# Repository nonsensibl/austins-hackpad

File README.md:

I just created a small macro pad with 8 switches and 8 rgb LEDs! I am a beginner and this is my first project.

I built this project because I have been very interested in the custom keyboard community for a while now and want to try my hands at it. I found this opportunity off of Instagram and I though it was a very cool thing I could do!

To use this, flash the firmware onto the macro pad and assemble with the sandwich mount design. The switches and LEDs need to be soldered onto the PCB and the keycaps go on at the end.

Challenges:

First: PCB design: KiCad

I had never touched a CAD software let alone designed a PCB. It started off generally easy with the PCB schematic which was self explanatory. However, next was the PCB editor. I spent almost 6 hours on this step. At first my switches and LEDs were in the wrong order, you couldn’t zigzag the LEDs or switches or else you would have a very hard time routing the PCB. Through trial and error, I learned how to route the PCB. 

Although it didn’t look the prettiest, I was proud of what I’d done. I learned some valuable problem solving skills and some very useful things from this. It took a lot of logic to figure out the routing. I also learned that the voltage and ground lines could be linked up line to line.

Second: Case Design

This was my first time doing any sort of 3D design. I first used Fusion360 but due to its limited capabilities, I decided to switch to Onshape. The design was actually fairly difficult and time consuming. This was also where the most math was used to center all the cutouts and make sure the clearances were correct. Compared to the PCB, it was less difficult but more time consuming.

https://cad.onshape.com/documents/ae2a962784265a0a15a314a3/w/fd7747368c903f62fc80b54c/e/c2a1514edb9aca260c24a683?renderMode=0&uiState=69d857150cda52f2ac39aa26 

Third: Firmware

This was actually the easiest part of the project. I just mapped each key to be an arbitrary macro key so the coding was very straight forward.

Summary:

I enjoyed this project a lot and learned a lot about 3D design, PCB design, and coding which I hope to use in other projects!

Materials: 
BOM:
8x Cherry MX Switches
8x SK6812 MINI-E LEDs
1x Seeeduino XIAO RP2040
8x Blank DCA Keycaps
4x M3 Screws
(Included in the kit)

Custom PCB
($5.12 from the HCB grant will be used)

Top Plate.step 
Bottom Plate.step
(Will be printed through printing legion) 

Others:
KMK Firmware

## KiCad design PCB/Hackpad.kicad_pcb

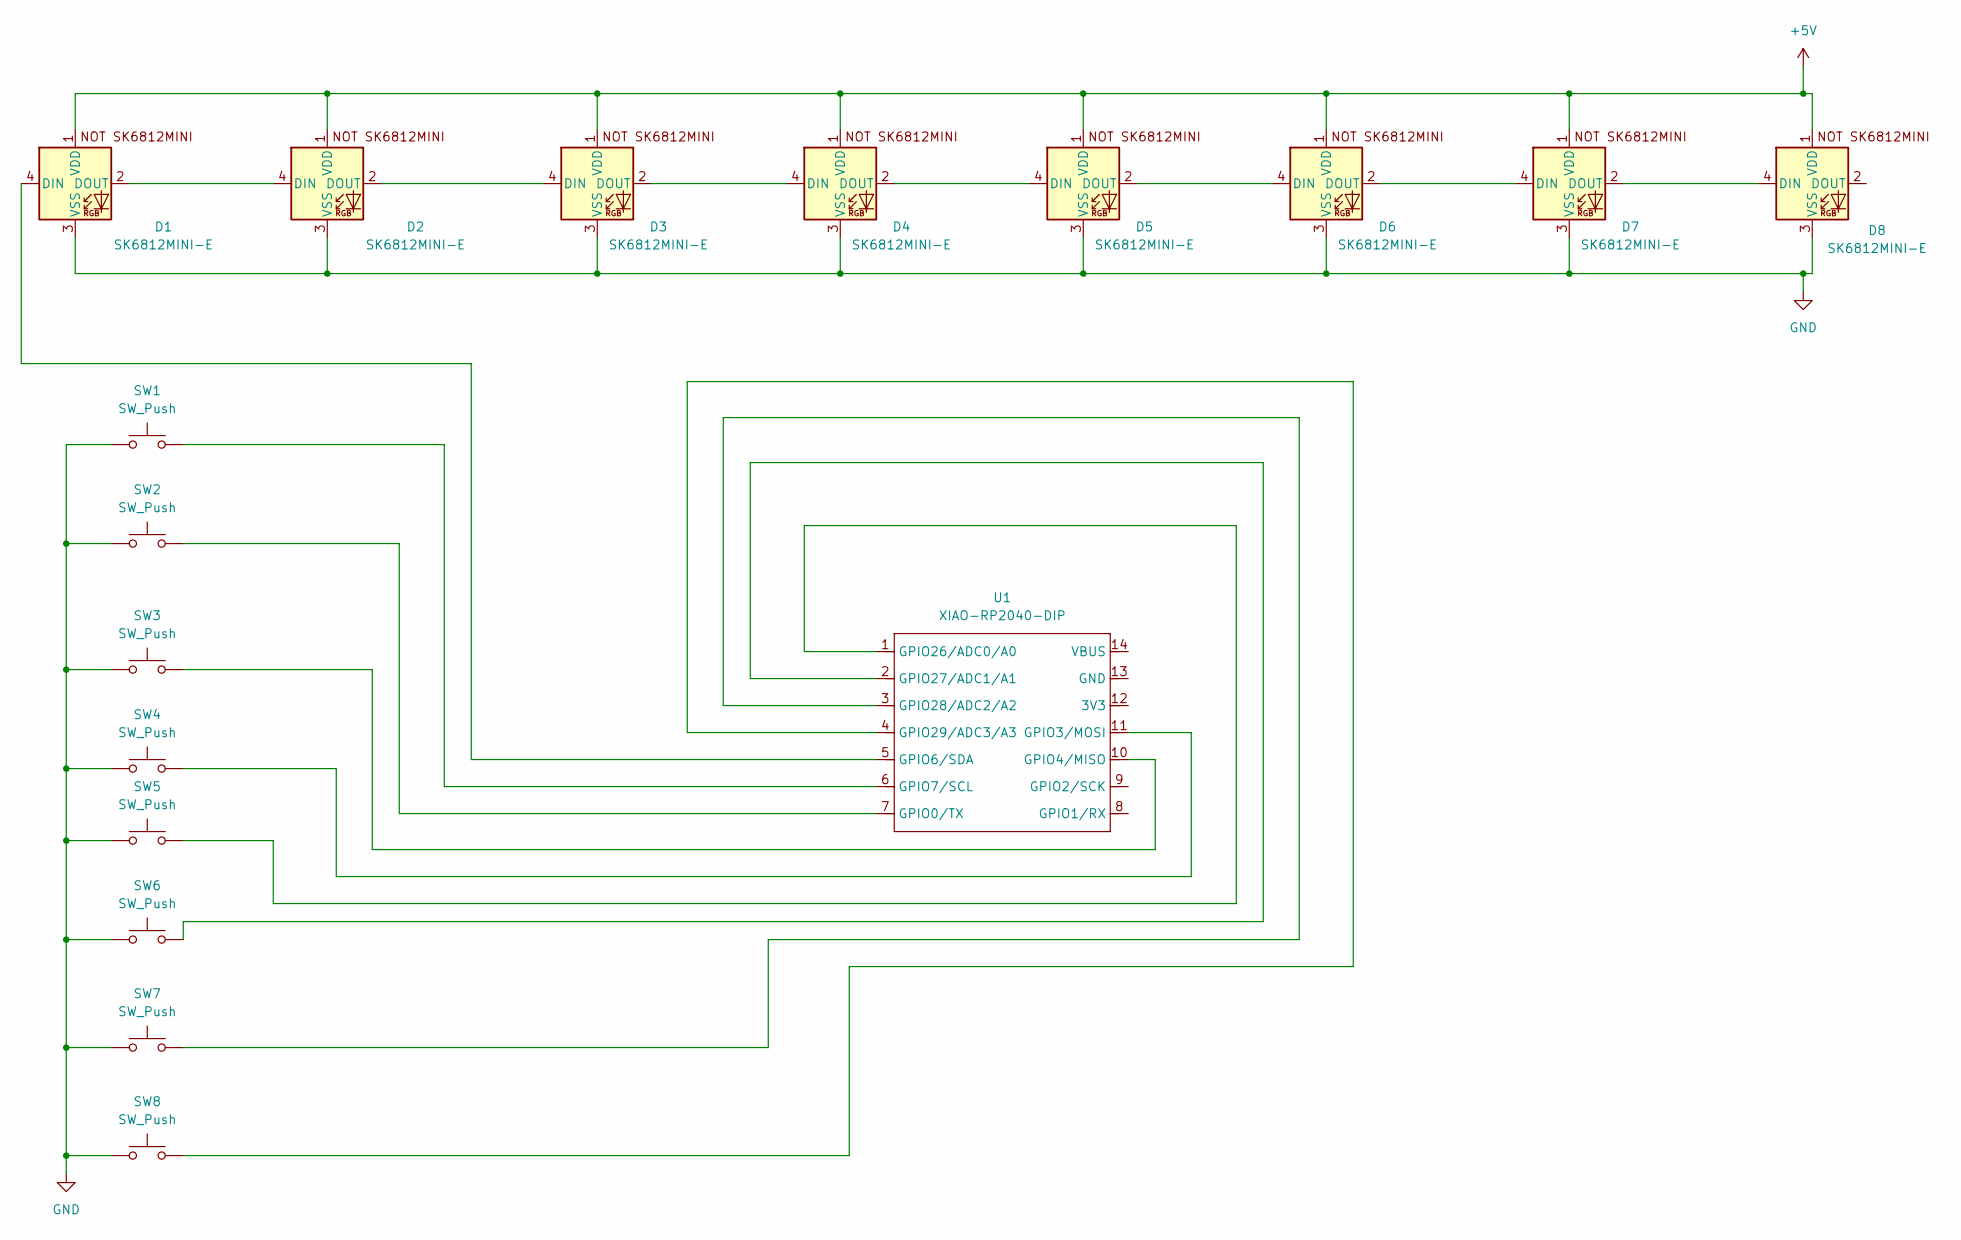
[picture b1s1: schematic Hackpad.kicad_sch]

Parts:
D1, D2, D3, D4, D5, D6, D7, D8: SK6812MINI-E; SK6812MINI-E_fixed
SW1, SW2, SW3, SW4, SW5, SW6, SW7, SW8: SW_Push; SW_Cherry_MX_1.00u_PCB
U1: XIAO-RP2040-DIP

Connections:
+5V: D1.1 (VDD), D2.1 (VDD), D3.1 (VDD), D4.1 (VDD), D5.1 (VDD), D6.1 (VDD), D7.1 (VDD), D8.1 (VDD)
GND: D1.3 (VSS), D2.3 (VSS), D3.3 (VSS), D4.3 (VSS), D5.3 (VSS), D6.3 (VSS), D7.3 (VSS), D8.3 (VSS), SW1.2, SW2.2, SW3.1, SW4.1, SW5.1, SW6.1, SW7.1, SW8.1
unnamed: D1.4 (DIN), U1.5 (GPIO6/SDA)
unnamed: D1.2 (DOUT), D2.4 (DIN)
unnamed: D2.2 (DOUT), D3.4 (DIN)
unnamed: D3.2 (DOUT), D4.4 (DIN)
unnamed: D4.2 (DOUT), D5.4 (DIN)
unnamed: D5.2 (DOUT), D6.4 (DIN)
unnamed: D6.2 (DOUT), D7.4 (DIN)
unnamed: D7.2 (DOUT), D8.4 (DIN)
unnamed: SW2.1, U1.7 (GPIO0/TX)
unnamed: SW4.2, U1.11 (GPIO3/MOSI)
unnamed: SW3.2, U1.10 (GPIO4/MISO)
unnamed: SW1.1, U1.6 (GPIO7/SCL)
unnamed: SW5.2, U1.1 (GPIO26/ADC0/A0)
unnamed: SW6.2, U1.2 (GPIO27/ADC1/A1)
unnamed: SW7.2, U1.3 (GPIO28/ADC2/A2)
unnamed: SW8.2, U1.4 (GPIO29/ADC3/A3)

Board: 2 copper layers, 17 parts (0 on the bottom side), 18 nets, no tracks yet.

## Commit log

2026-03-29 Add files via upload
    CAD assembly STEP file
2026-03-29 Rename austins-hackpad.step to CAD/austins-hackpad.step
2026-03-29 Rename austins-hackpad.step to austins-hackpadfull.step
2026-03-29 Rename hackpad - hackpad.step to austins-hackpad-bottom-case.step
2026-03-29 Rename austins-hackpadfull.step to austins-hackpad-full.step
2026-03-29 Rename hackpad - Part 3.step to austins-hackpad-modelpcb.step
2026-03-29 Rename hackpad - hackpad (1).step to austins-hackpad-lid.step
2026-03-29 Rename austins-hackpad-full.step to austins-hackpad-fulldesign.step
2026-03-29 Rename Hackpad.kicad_pcb to PCB/Hackpad.kicad_pcb
2026-03-29 Rename Hackpad.kicad_pro to PCB/Hackpad.kicad_pro
2026-03-29 Rename Hackpad.kicad_sch to PCB/Hackpad.kicad_sch
2026-03-29 Rename fp-info-cache to PCB/fp-info-cache
2026-03-29 Rename fp-lib-table to PCB/fp-lib-table
2026-03-29 Rename sym-lib-table to PCB/sym-lib-table
2026-03-29 Rename hackpad - austins-hackpad-lid.step to austins-hackpad-lid.step
2026-03-29 Rename hackpad (1).step to austins-hackpad-fullbody.step
2026-03-30 Rename hackpad - austins-hackpad-bottom-case.step to austins-hackpad-bottom-case.step
2026-03-30 Rename code.py to main.py
2026-04-10 Rename Hackpad 1 (1).step to austins-hackpadfull.step
2026-04-15 Rename gerbers.zip to PCB/gerbers.zip
